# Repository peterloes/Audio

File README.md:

# Audio
 designed with MOMO 
 
Authors: Loës P., Kempenaers B.(2020) 

Firmware not reviewed. 

Platform for animal observation and manipulation.

Supported:
- FN-RM01 MP3/WAV Audio Recorder and Player Module (Website: www.flyrontech.com)

The Project is used to playback and record sounds, target manipulated via pit-tag numbers.
Uses the Audio Module FN-RM01 which handles automatic playback and record files.

An efficient application to monitor and control animal behaviour in wildlife
as well as in laboratory settings

-	Targeted manipulation of 1000 and more individuals
- Pit-tag numbers targeting Playback-Soundfiles or Record-Soundfiles 
- Playback Audio files P001.wav/mp3 up to P005.wav/mp3 over time
- Random Playback Audio files P001.wav/mp3 up to P005.wav/mp3 over time
- Record Audio files R001.wav up to R999.wav over time
- Combined Audio Playback and Record over time
- There are two special IDs:

  "ANY" means there was a transponder detected, but its ID is not listed.

  "UNKNOWN" means that NO transponder could be detected

-	Low power consumption and specific data collection lead to long lasting collection periods
-	Applicable world-wide due to its compatibility with different types of radio clock receivers 
-	Data-transfer to external devices, such as personal computers
- Time Synchronization with atomic clock once a day to ensure optimal data quality
- Application Current Control twice a day
- Forecast for Battery-Change implemented
- Energy Bypass so that Date and Time are maintained even when changing battery
- Hyperterminal Output to get real-time data to the computer/laptop

Prototype: Smart Nest Box with microphone and speaker on top

https://github.com/peterloes/Audio/blob/master/Getting_Started_Tutorial/1_poster_overview.pdf

Raw data on SD Card:

https://github.com/peterloes/Audio/blob/master/Getting_Started_Tutorial/6_raw_data.txt

Configuration data on SD Card:

https://github.com/peterloes/Audio/blob/master/Software/CONFIG.TXT

Mainboard:

https://github.com/peterloes/MOMO

Optional components:

https://github.com/peterloes/Booter_RFID-MS_MOMO_TAMDL

https://github.com/peterloes/Clock_receiver_RFID-MS_MOMO_TAMDL

Manufacture:

https://github.com/peterloes/Audio/blob/master/Getting_Started_Tutorial/5_Supplier.txt

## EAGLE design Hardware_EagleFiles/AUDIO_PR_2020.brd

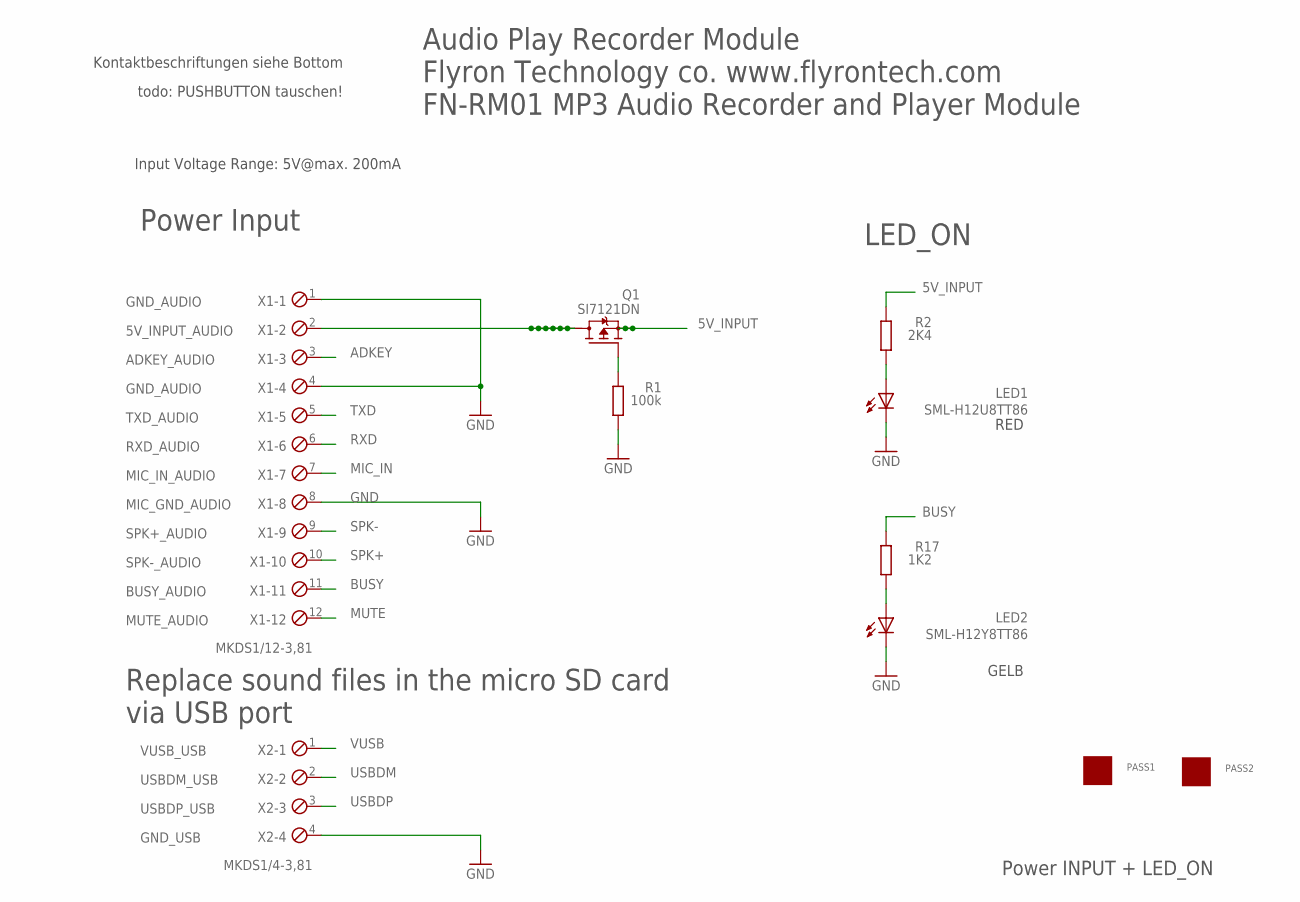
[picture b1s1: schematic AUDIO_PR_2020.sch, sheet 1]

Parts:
LED1: SML-H12U8TT86; CHIPLED_0805
LED2: SML-H12Y8TT86; CHIPLED_0805
PASS1, PASS2: ROUND_1MM1.5; ROUND2_1.5MM
Q1: SI7121DN; TRANSISTOR-FET_1212-8S
R1: 100k; R0805
R2: 2K4; R0805
R17: 1K2; R0805
X1: MKDS1/12-3,81; 12POL381
X2: MKDS1/4-3,81; 4POL381

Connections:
5V_INPUT: Q1.1 (S), Q1.2 (S), Q1.3 (S), R2.1; also elsewhere on the board
5V_INPUT_AUDIO: Q1.5 (D), Q1.6 (D), Q1.7 (D), Q1.8 (D), Q1.9 (D), Q1.10 (D), Q1.11 (D), X1.2
ADKEY: X1.3; also elsewhere on the board
BUSY: R17.1, X1.11; also elsewhere on the board
GND: LED1.C, LED2.C, R1.1, X1.1, X1.4, X1.8, X2.4; also elsewhere on the board
MIC_IN: X1.7; also elsewhere on the board
MUTE: X1.12; also elsewhere on the board
unnamed: LED2.A, R17.2
unnamed: Q1.4 (G), R1.2
unnamed: LED1.A, R2.2
RXD: X1.6; also elsewhere on the board
SPK+: X1.10; also elsewhere on the board
SPK-: X1.9; also elsewhere on the board
TXD: X1.5; also elsewhere on the board
USBDM: X2.2; also elsewhere on the board
USBDP: X2.3; also elsewhere on the board
VUSB: X2.1; also elsewhere on the board

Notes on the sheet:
GND_AUDIO
Input Voltage Range: 5V@max. 200mA
5V_INPUT_AUDIO
Power INPUT + LED_ON
Power Input
Audio Play Recorder Module Flyron Technology co. www.flyrontech.com FN-RM01 MP3 Audio Recorder and Player Module
LED_ON
RED
ADKEY_AUDIO
TXD_AUDIO
RXD_AUDIO
MIC_IN_AUDIO
MIC_GND_AUDIO
SPK+_AUDIO
SPK-_AUDIO
BUSY_AUDIO
VUSB_USB
USBDM_USB
USBDP_USB
GND_USB
Replace sound files in the micro SD card via USB port
MUTE_AUDIO
Kontaktbeschriftungen siehe Bottom
todo: PUSHBUTTON tauschen!
GELB

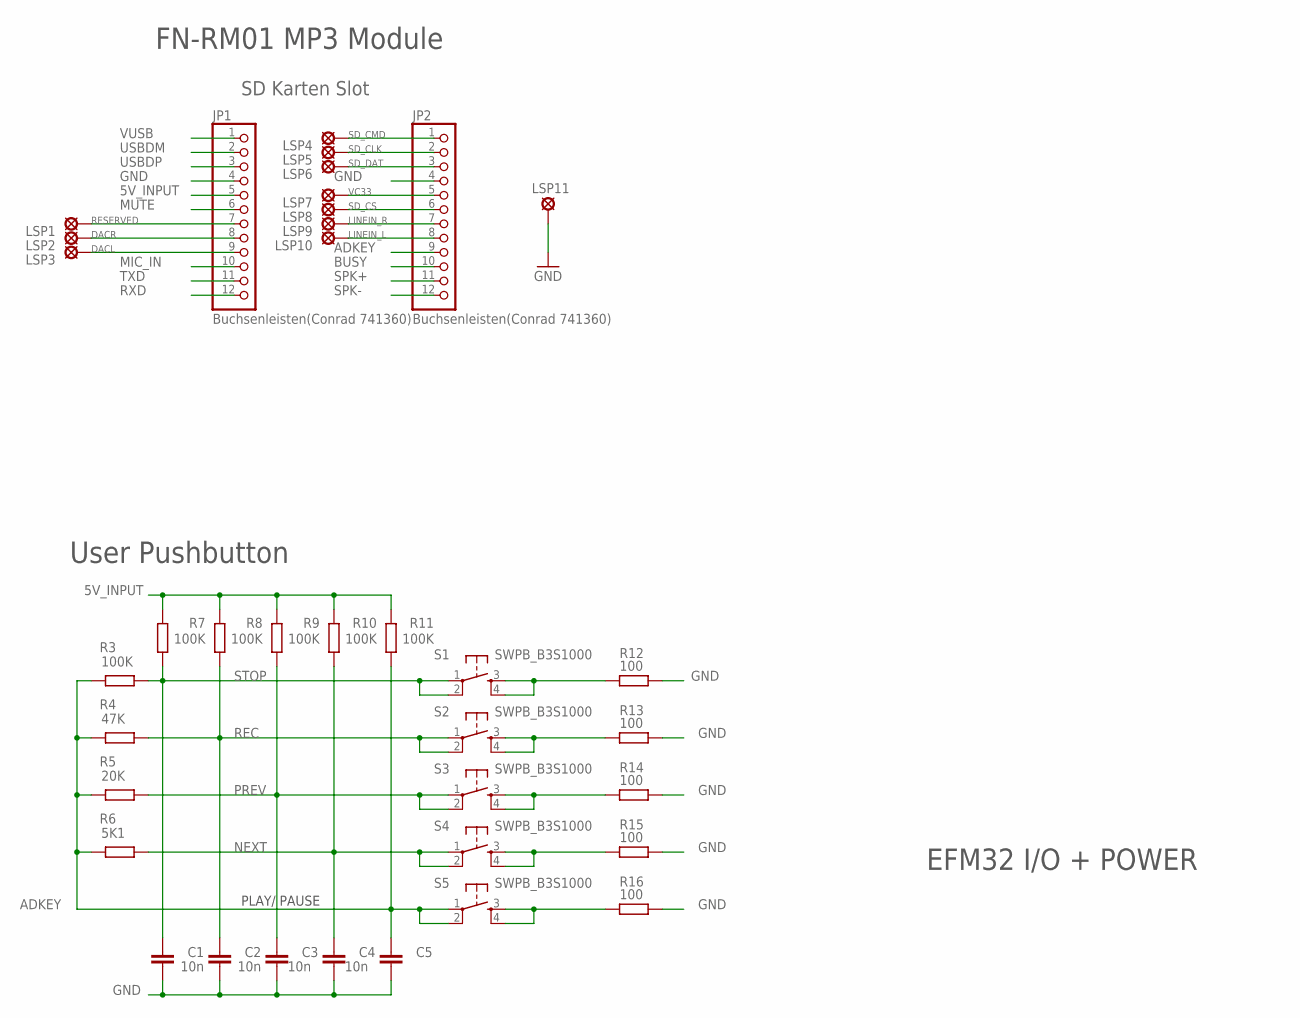
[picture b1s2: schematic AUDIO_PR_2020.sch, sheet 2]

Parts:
C1, C2, C3, C4, C5: 10n; C0603
JP1, JP2: Buchsenleisten(Conrad 741360); 1X12
LSP1, LSP2, LSP3, LSP4, LSP5, LSP6, LSP7, LSP8, LSP9, LSP10, LSP11: LSP10
R3, R7, R8, R9, R10, R11: 100K; R0805
R4: 47K; R0805
R5: 20K; R0805
R6: 5K1; R0805
R12, R13, R14, R15, R16: 100; R0805
S1, S2, S3, S4, S5: SWPB_B3S1000; DTSM-6

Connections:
5V_INPUT: JP1.5, R7.2, R8.2, R9.2, R10.2, R11.2; also elsewhere on the board
ADKEY: C5.2, JP2.9, R3.2, R4.2, R5.2, R6.2, R11.1, S5.1, S5.2; also elsewhere on the board
BUSY: JP2.10; also elsewhere on the board
DACL: JP1.9, LSP3.MP
DACR: JP1.8, LSP2.MP
GND: C1.1, C2.1, C3.1, C4.1, C5.1, JP1.4, JP2.4, LSP11.MP, R12.2, R13.2, R14.2, R15.2, R16.2; also elsewhere on the board
LINEIN_L: JP2.8, LSP10.MP
LINEIN_R: JP2.7, LSP9.MP
MIC_IN: JP1.10; also elsewhere on the board
MUTE: JP1.6; also elsewhere on the board
unnamed: R14.1, S3.3, S3.4
unnamed: R15.1, S4.3, S4.4
unnamed: R16.1, S5.3, S5.4
unnamed: R12.1, S1.3, S1.4
unnamed: R13.1, S2.3, S2.4
NEXT: C4.2, R6.1, R10.1, S4.1, S4.2
PREV: C3.2, R5.1, R9.1, S3.1, S3.2
REC: C2.2, R4.1, R8.1, S2.1, S2.2
RESERVED: JP1.7, LSP1.MP
RXD: JP1.12; also elsewhere on the board
SD_CLK: JP2.2, LSP5.MP
SD_CMD: JP2.1, LSP4.MP
SD_CS: JP2.6, LSP8.MP
SD_DAT: JP2.3, LSP6.MP
SPK+: JP2.11; also elsewhere on the board
SPK-: JP2.12; also elsewhere on the board
STOP: C1.2, R3.1, R7.1, S1.1, S1.2
TXD: JP1.11; also elsewhere on the board
USBDM: JP1.2; also elsewhere on the board
USBDP: JP1.3; also elsewhere on the board
VC33: JP2.5, LSP7.MP
VUSB: JP1.1; also elsewhere on the board

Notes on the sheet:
EFM32 I/O + POWER
User Pushbutton
SD Karten Slot
FN-RM01 MP3 Module
PLAY/ PAUSE

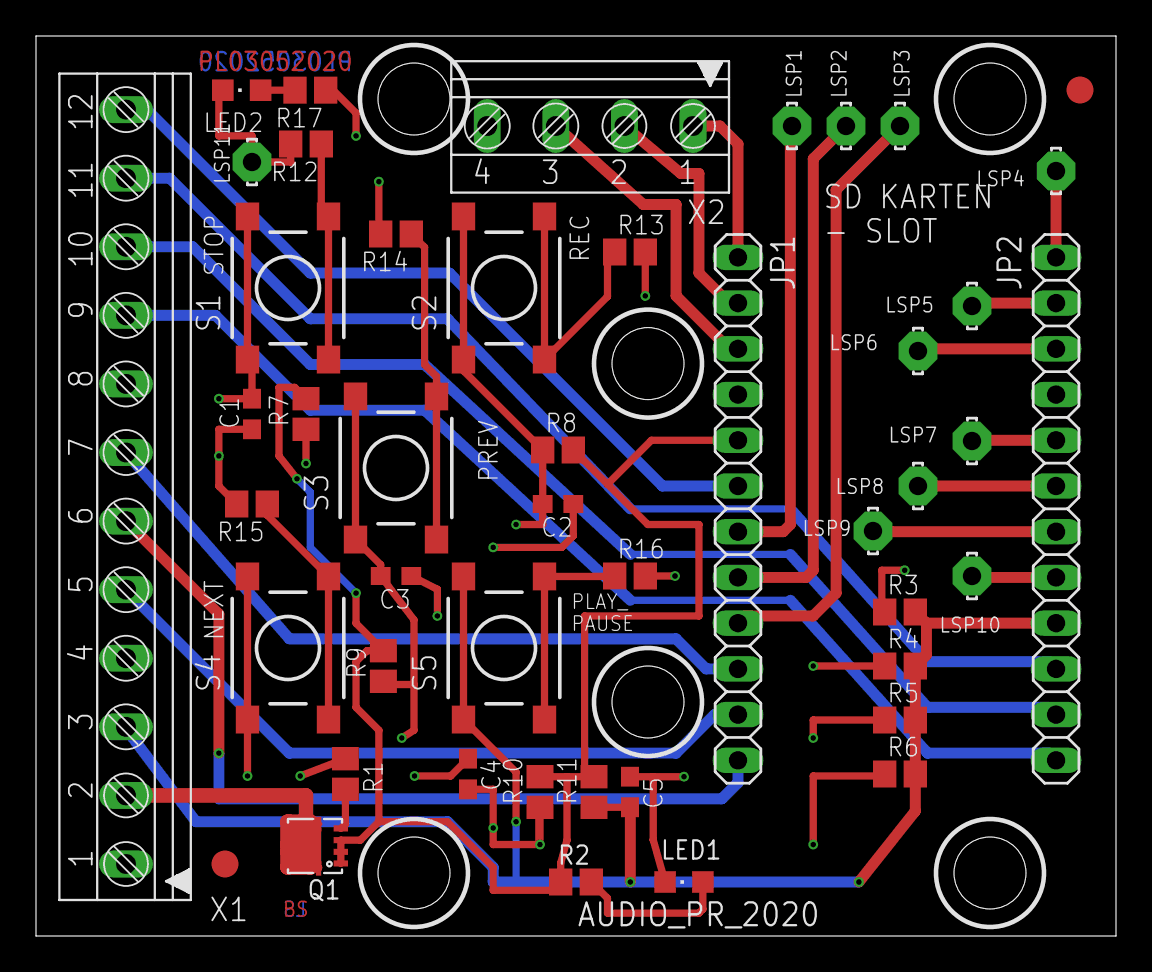
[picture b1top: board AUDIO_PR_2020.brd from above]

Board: 4 copper layers, 60.0 x 50.0 mm, 47 parts (0 on the bottom side), 36 nets.

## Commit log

2020-11-11 Create armgcc

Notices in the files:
parts and their libraries:
SparkFun-Aesthetics: Licensing: CC v3.0 Share-Alike You are welcome to use this library for commercial purposes.
